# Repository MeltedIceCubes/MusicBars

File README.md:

# MusicBars
Tri-Channel Volume indicator board

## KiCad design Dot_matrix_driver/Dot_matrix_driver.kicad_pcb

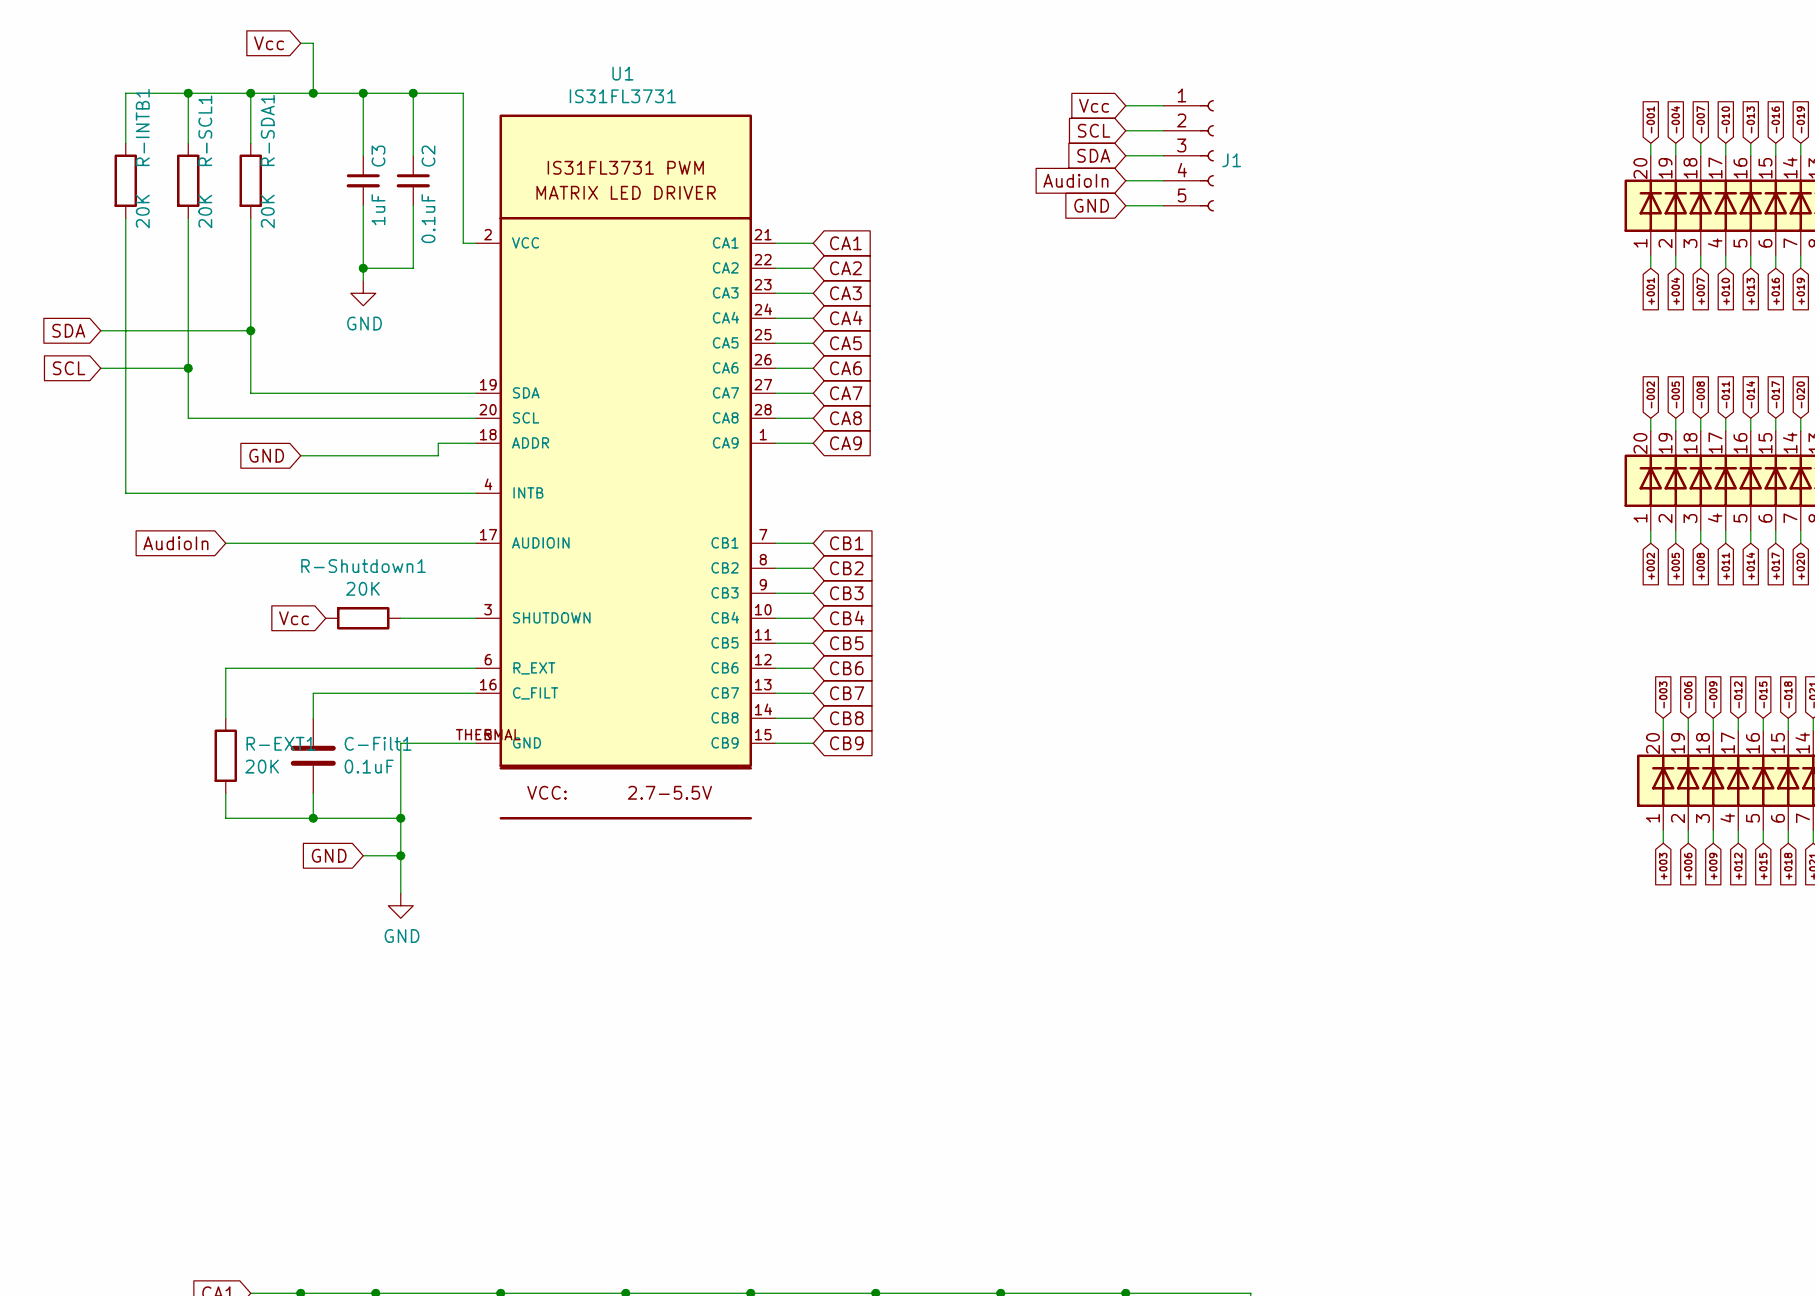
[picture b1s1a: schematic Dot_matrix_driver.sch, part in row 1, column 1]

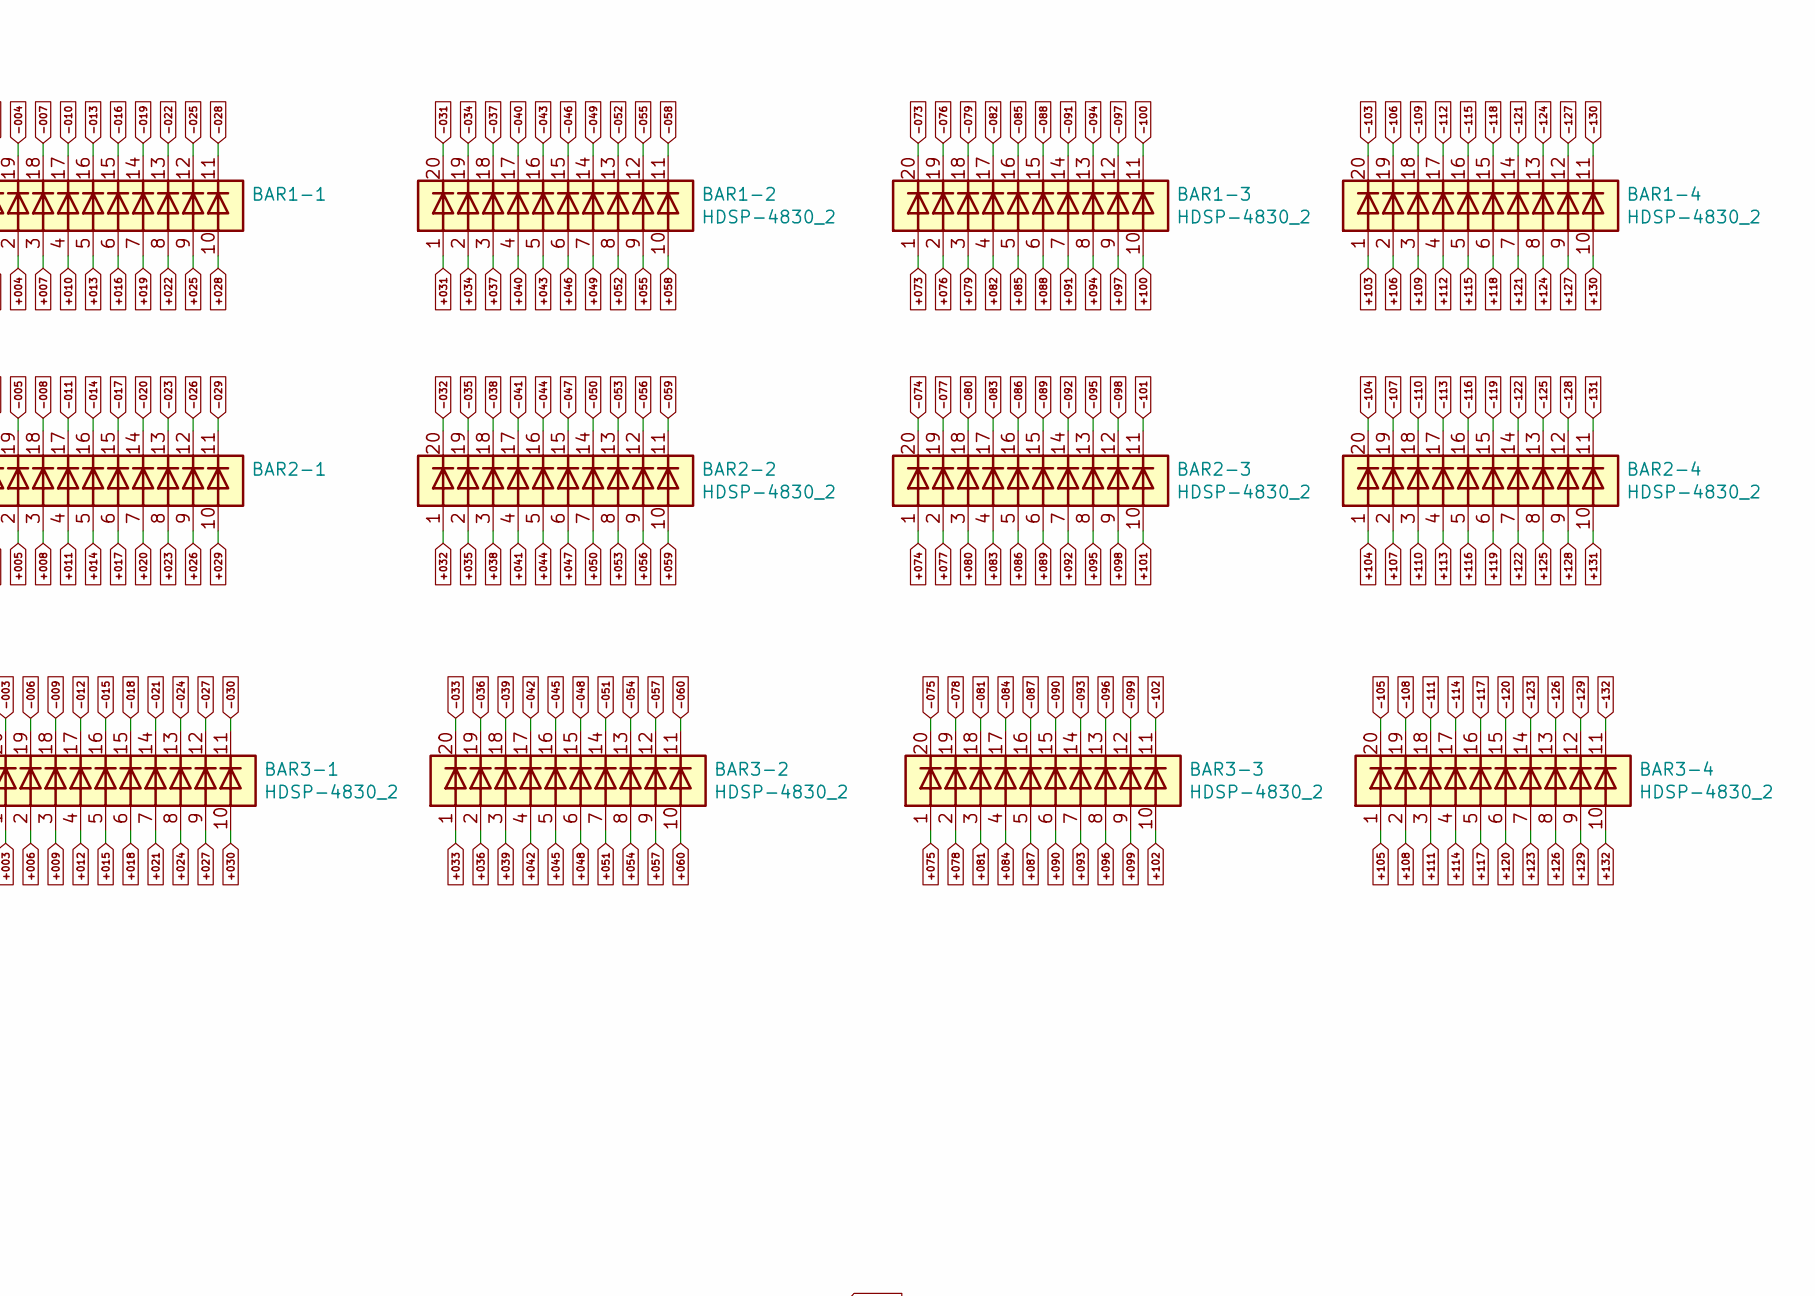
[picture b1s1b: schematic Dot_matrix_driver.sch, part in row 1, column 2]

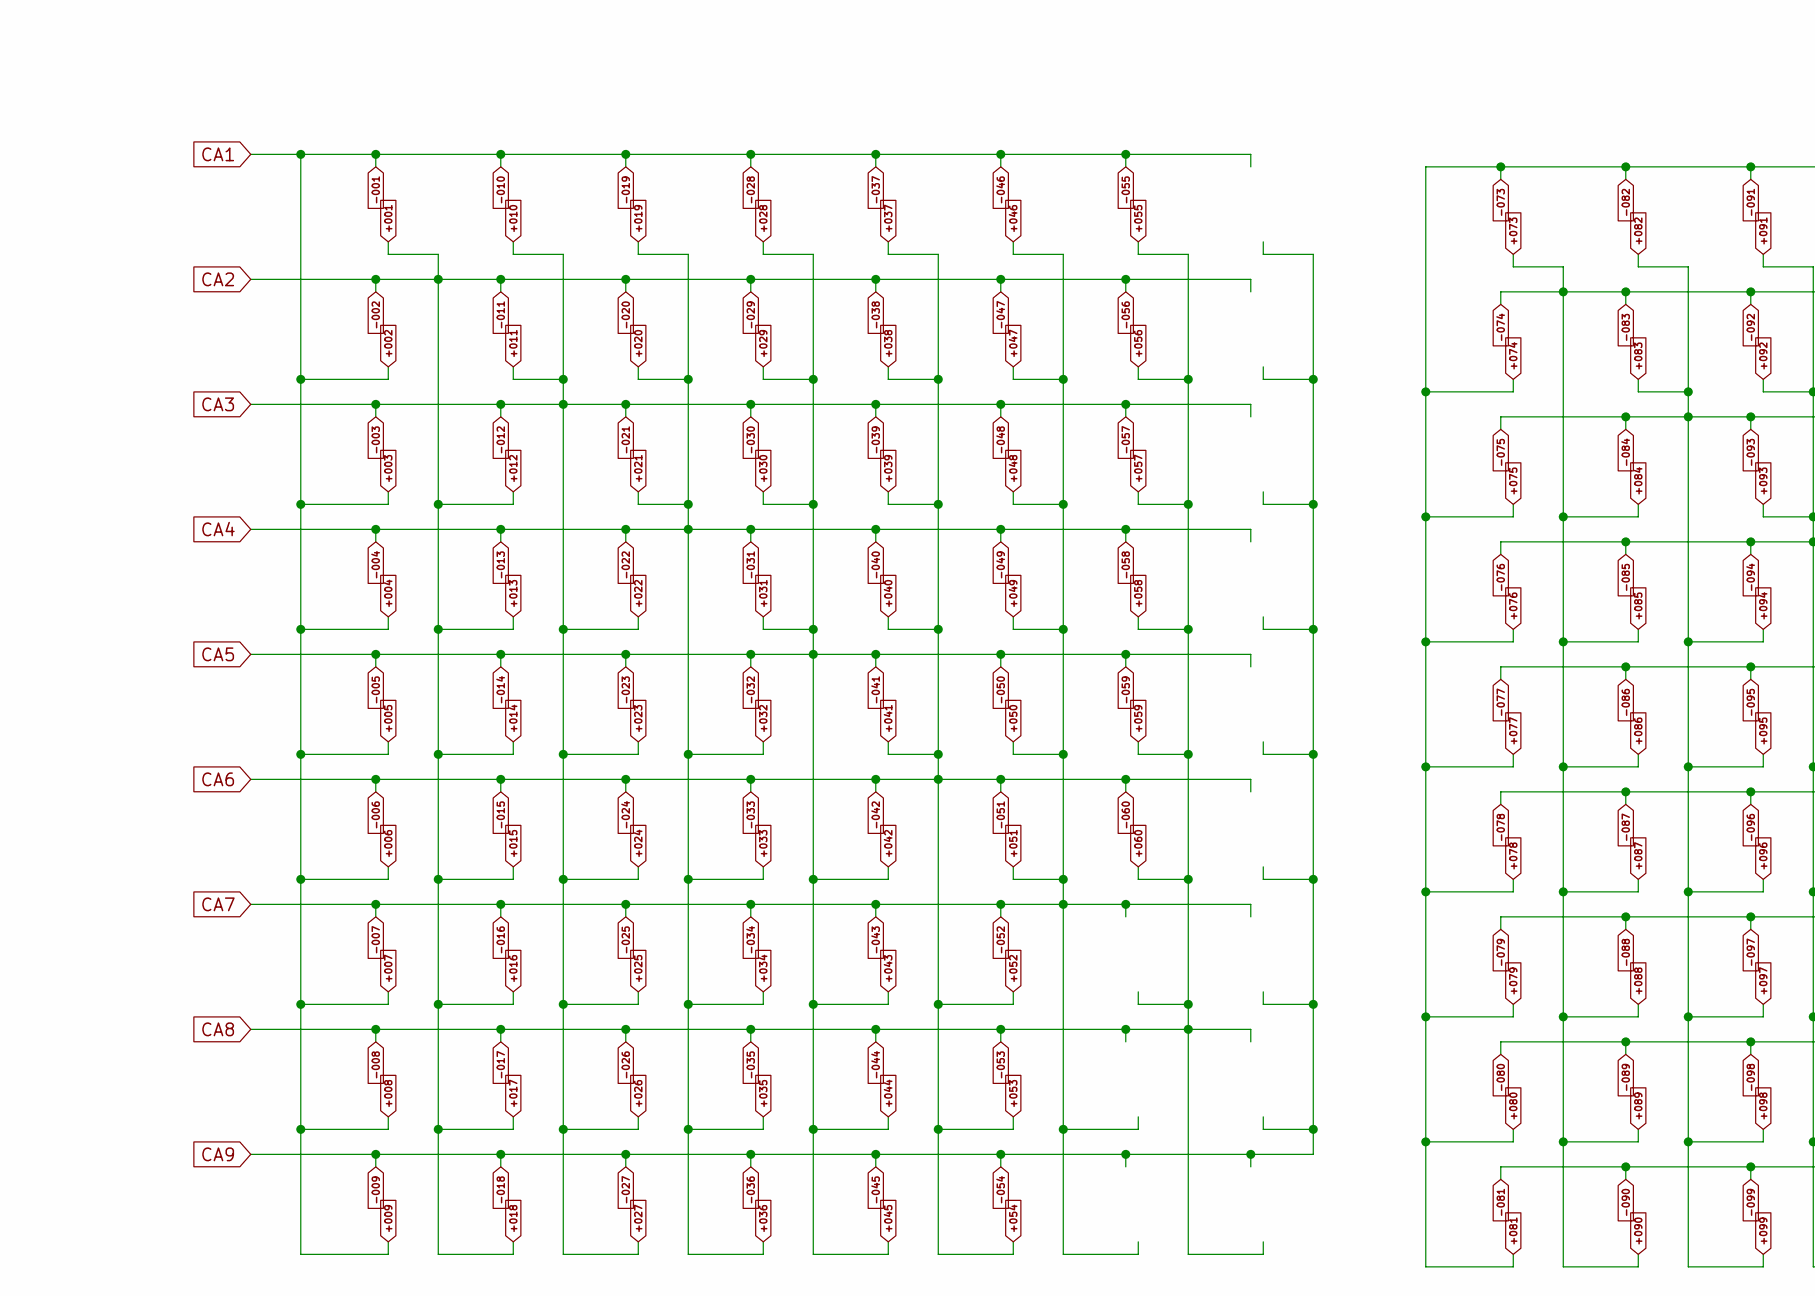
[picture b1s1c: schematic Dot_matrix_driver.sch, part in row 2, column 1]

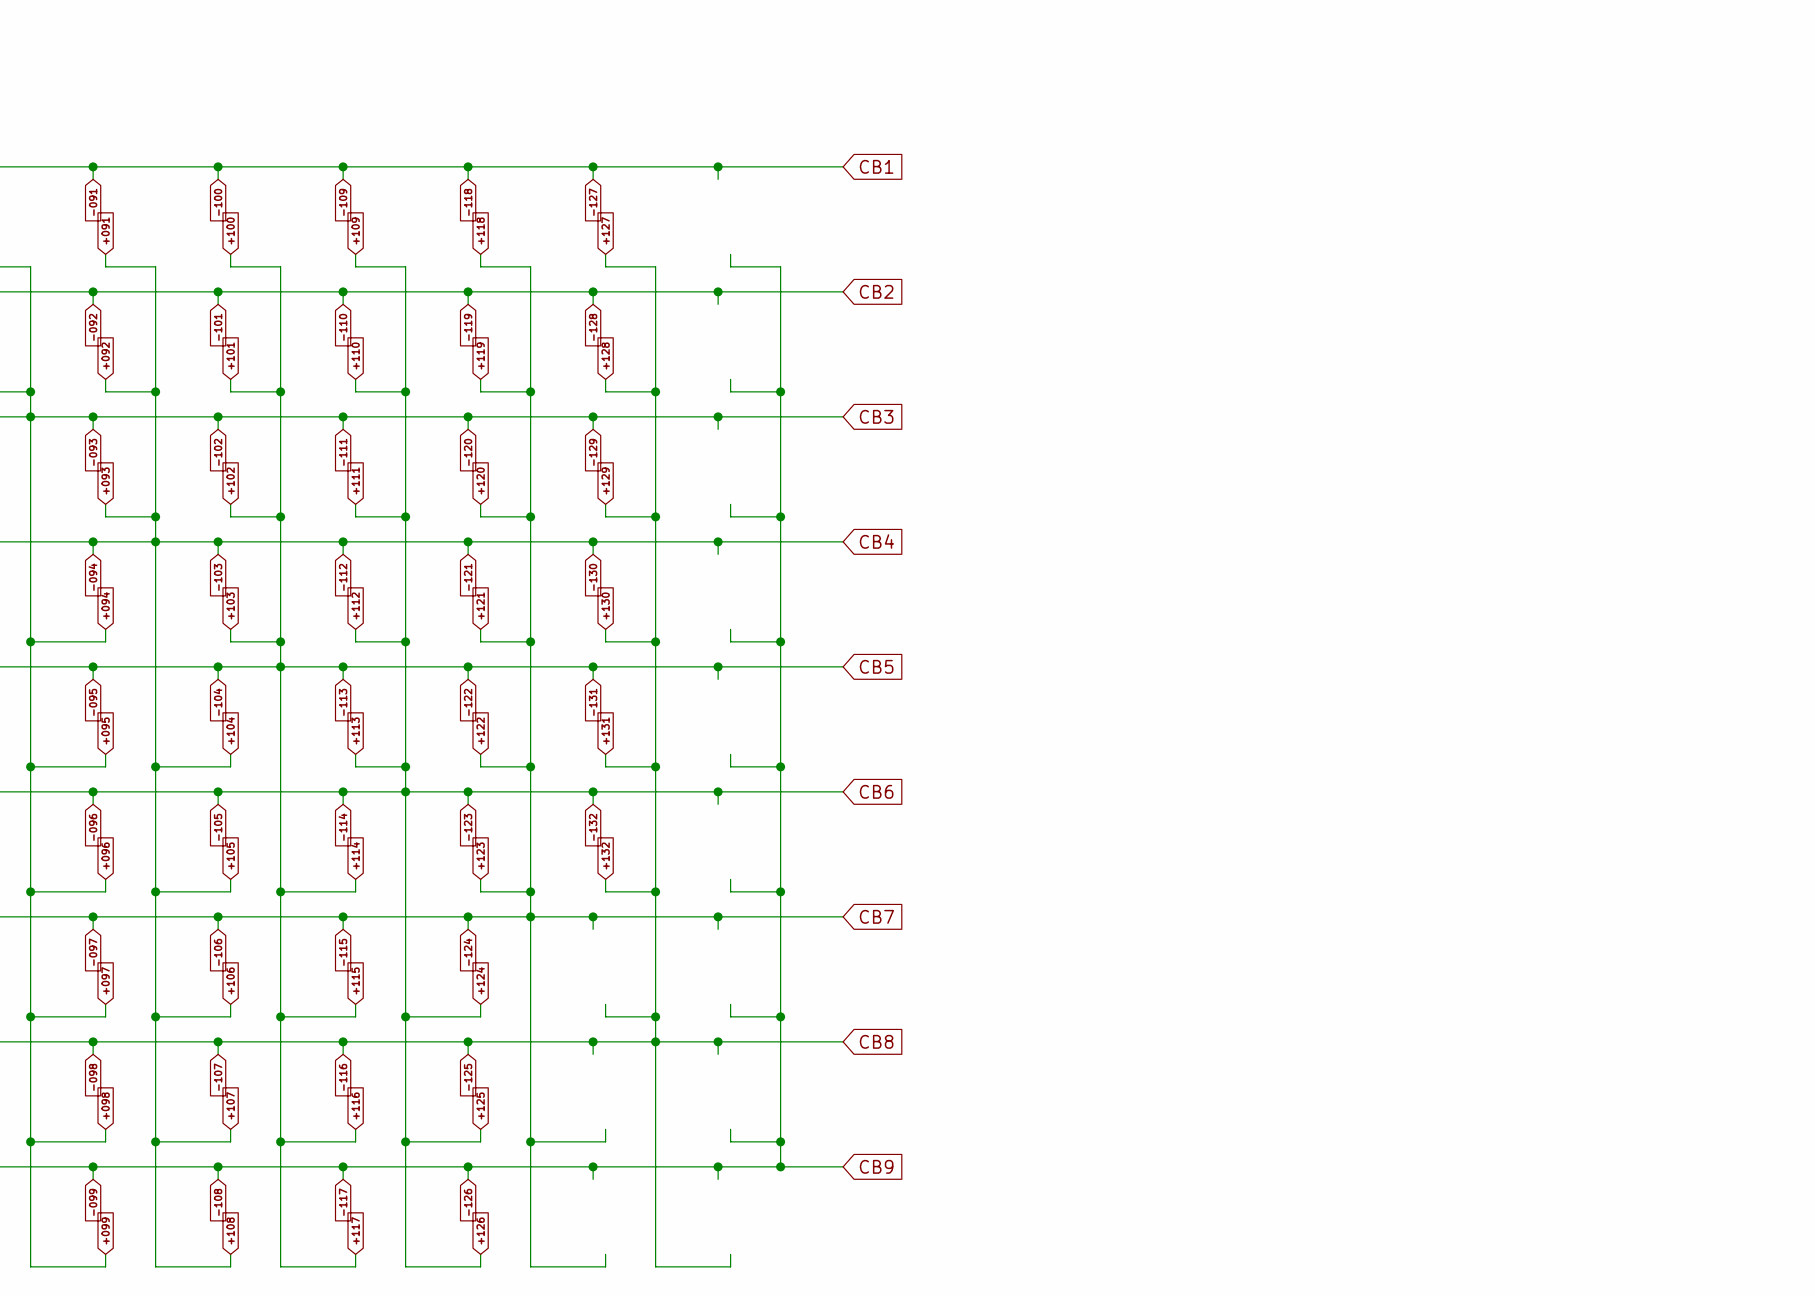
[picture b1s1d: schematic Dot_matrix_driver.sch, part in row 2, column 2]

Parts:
BAR1-1, BAR1-2, BAR1-3, BAR1-4, BAR2-1, BAR2-2, BAR2-3, BAR2-4, BAR3-1, BAR3-2, BAR3-3, BAR3-4: HDSP-4830_2; HDSP-48xx
C2: 0.1uF; C_Disc_D5.1mm_W3.2mm_P5.00mm
C3: 1uF; C_Disc_D5.1mm_W3.2mm_P5.00mm
C-Filt1: 0.1uF; C_Disc_D5.1mm_W3.2mm_P5.00mm
J1: Conn_01x05_Female; PinHeader_1x05_P2.54mm_Vertical
R-EXT1: 20K; R_Axial_DIN0207_L6.3mm_D2.5mm_P10.16mm_Horizontal
R-INTB1: 20K; R_Axial_DIN0207_L6.3mm_D2.5mm_P10.16mm_Horizontal
R-SCL1: 20K; R_Axial_DIN0207_L6.3mm_D2.5mm_P10.16mm_Horizontal
R-SDA1: 20K; R_Axial_DIN0207_L6.3mm_D2.5mm_P10.16mm_Horizontal
R-Shutdown1: 20K; R_Axial_DIN0207_L6.3mm_D2.5mm_P10.16mm_Horizontal
U1: IS31FL3731; QFN28_4MM_0.4MM

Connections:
+001: BAR1-1.1 (A), BAR1-1.5 (A), BAR1-1.6 (A), BAR2-1.5 (A), BAR2-1.6 (A), BAR2-1.11 (K), BAR2-1.14 (K), BAR2-1.17 (K), BAR2-1.20 (K), BAR2-2.12 (K), BAR2-2.15 (K), BAR2-2.18 (K), BAR3-1.4 (A), BAR3-1.5 (A), BAR3-1.6 (A), U1.22 (CA2)
+002: BAR1-1.2 (A), BAR1-1.3 (A), BAR1-1.11 (K), BAR1-1.14 (K), BAR1-1.17 (K), BAR1-1.20 (K), BAR1-2.12 (K), BAR1-2.15 (K), BAR1-2.18 (K), BAR2-1.1 (A), BAR2-1.2 (A), BAR2-1.3 (A), BAR3-1.1 (A), BAR3-1.2 (A), BAR3-1.3 (A), U1.21 (CA1)
+010: BAR1-1.4 (A), BAR1-1.8 (A), BAR1-1.9 (A), BAR2-1.4 (A), BAR2-1.8 (A), BAR2-1.9 (A), BAR3-1.8 (A), BAR3-1.9 (A), BAR3-1.11 (K), BAR3-1.14 (K), BAR3-1.17 (K), BAR3-1.20 (K), BAR3-2.12 (K), BAR3-2.15 (K), BAR3-2.18 (K), U1.23 (CA3)
+019: BAR1-1.7 (A), BAR1-1.13 (K), BAR1-1.16 (K), BAR1-1.19 (K), BAR1-2.2 (A), BAR1-2.11 (K), BAR1-2.14 (K), BAR1-2.17 (K), BAR1-2.20 (K), BAR2-1.7 (A), BAR2-2.1 (A), BAR2-2.2 (A), BAR3-1.7 (A), BAR3-2.1 (A), BAR3-2.2 (A), U1.24 (CA4)
+028: BAR1-1.10 (A), BAR1-2.1 (A), BAR1-2.5 (A), BAR2-1.10 (A), BAR2-1.13 (K), BAR2-1.16 (K), BAR2-1.19 (K), BAR2-2.5 (A), BAR2-2.11 (K), BAR2-2.14 (K), BAR2-2.17 (K), BAR2-2.20 (K), BAR3-1.10 (A), BAR3-2.4 (A), BAR3-2.5 (A), U1.25 (CA5)
+037: BAR1-2.3 (A), BAR1-2.4 (A), BAR1-2.8 (A), BAR2-2.3 (A), BAR2-2.4 (A), BAR2-2.8 (A), BAR3-1.13 (K), BAR3-1.16 (K), BAR3-1.19 (K), BAR3-2.3 (A), BAR3-2.8 (A), BAR3-2.11 (K), BAR3-2.14 (K), BAR3-2.17 (K), BAR3-2.20 (K), U1.26 (CA6)
+046: BAR1-1.12 (K), BAR1-1.15 (K), BAR1-1.18 (K), BAR1-2.6 (A), BAR1-2.7 (A), BAR1-2.13 (K), BAR1-2.16 (K), BAR1-2.19 (K), BAR2-2.6 (A), BAR2-2.7 (A), BAR3-2.6 (A), BAR3-2.7 (A), U1.27 (CA7)
+055: BAR1-2.9 (A), BAR1-2.10 (A), BAR2-1.12 (K), BAR2-1.15 (K), BAR2-1.18 (K), BAR2-2.9 (A), BAR2-2.10 (A), BAR2-2.13 (K), BAR2-2.16 (K), BAR2-2.19 (K), BAR3-2.9 (A), BAR3-2.10 (A), U1.28 (CA8)
+073: BAR1-3.1 (A), BAR1-3.5 (A), BAR1-3.6 (A), BAR2-3.5 (A), BAR2-3.6 (A), BAR2-3.11 (K), BAR2-3.14 (K), BAR2-3.17 (K), BAR2-3.20 (K), BAR2-4.12 (K), BAR2-4.15 (K), BAR2-4.18 (K), BAR3-3.4 (A), BAR3-3.5 (A), BAR3-3.6 (A), U1.8 (CB2)
+074: BAR1-3.2 (A), BAR1-3.3 (A), BAR1-3.11 (K), BAR1-3.14 (K), BAR1-3.17 (K), BAR1-3.20 (K), BAR1-4.12 (K), BAR1-4.15 (K), BAR1-4.18 (K), BAR2-3.1 (A), BAR2-3.2 (A), BAR2-3.3 (A), BAR3-3.1 (A), BAR3-3.2 (A), BAR3-3.3 (A), U1.7 (CB1)
+082: BAR1-3.4 (A), BAR1-3.8 (A), BAR1-3.9 (A), BAR2-3.4 (A), BAR2-3.8 (A), BAR2-3.9 (A), BAR3-3.8 (A), BAR3-3.9 (A), BAR3-3.11 (K), BAR3-3.14 (K), BAR3-3.17 (K), BAR3-3.20 (K), BAR3-4.12 (K), BAR3-4.15 (K), BAR3-4.18 (K), U1.9 (CB3)
+091: BAR1-3.7 (A), BAR1-3.13 (K), BAR1-3.16 (K), BAR1-3.19 (K), BAR1-4.2 (A), BAR1-4.11 (K), BAR1-4.14 (K), BAR1-4.17 (K), BAR1-4.20 (K), BAR2-3.7 (A), BAR2-4.1 (A), BAR2-4.2 (A), BAR3-3.7 (A), BAR3-4.1 (A), BAR3-4.2 (A), U1.10 (CB4)
+100: BAR1-3.10 (A), BAR1-4.1 (A), BAR1-4.5 (A), BAR2-3.10 (A), BAR2-3.13 (K), BAR2-3.16 (K), BAR2-3.19 (K), BAR2-4.5 (A), BAR2-4.11 (K), BAR2-4.14 (K), BAR2-4.17 (K), BAR2-4.20 (K), BAR3-3.10 (A), BAR3-4.4 (A), BAR3-4.5 (A), U1.11 (CB5)
+109: BAR1-4.3 (A), BAR1-4.4 (A), BAR1-4.8 (A), BAR2-4.3 (A), BAR2-4.4 (A), BAR2-4.8 (A), BAR3-3.13 (K), BAR3-3.16 (K), BAR3-3.19 (K), BAR3-4.3 (A), BAR3-4.8 (A), BAR3-4.11 (K), BAR3-4.14 (K), BAR3-4.17 (K), BAR3-4.20 (K), U1.12 (CB6)
+118: BAR1-3.12 (K), BAR1-3.15 (K), BAR1-3.18 (K), BAR1-4.6 (A), BAR1-4.7 (A), BAR1-4.13 (K), BAR1-4.16 (K), BAR1-4.19 (K), BAR2-4.6 (A), BAR2-4.7 (A), BAR3-4.6 (A), BAR3-4.7 (A), U1.13 (CB7)
+127: BAR1-4.9 (A), BAR1-4.10 (A), BAR2-3.12 (K), BAR2-3.15 (K), BAR2-3.18 (K), BAR2-4.9 (A), BAR2-4.10 (A), BAR2-4.13 (K), BAR2-4.16 (K), BAR2-4.19 (K), BAR3-4.9 (A), BAR3-4.10 (A), U1.14 (CB8)
-009: BAR3-1.12 (K), BAR3-1.15 (K), BAR3-1.18 (K), BAR3-2.13 (K), BAR3-2.16 (K), BAR3-2.19 (K), U1.1 (CA9)
-081: BAR3-3.12 (K), BAR3-3.15 (K), BAR3-3.18 (K), BAR3-4.13 (K), BAR3-4.16 (K), BAR3-4.19 (K), U1.15 (CB9)
AudioIn: J1.4, U1.17 (AUDIOIN)
GND: C2.2, C3.2, C-Filt1.2, J1.5, R-EXT1.2, U1.5 (GND), U1.18 (ADDR), U1.THERMAL (GND)
unnamed: C-Filt1.1, U1.16 (C_FILT)
unnamed: R-EXT1.1, U1.6 (R_EXT)
unnamed: R-INTB1.2, U1.4 (INTB)
unnamed: R-Shutdown1.1, U1.3 (SHUTDOWN)
SCL: J1.2, R-SCL1.2, U1.20 (SCL)
SDA: J1.3, R-SDA1.2, U1.19 (SDA)
Vcc: C2.1, C3.1, J1.1, R-INTB1.1, R-SCL1.1, R-SDA1.1, R-Shutdown1.2, U1.2 (VCC)

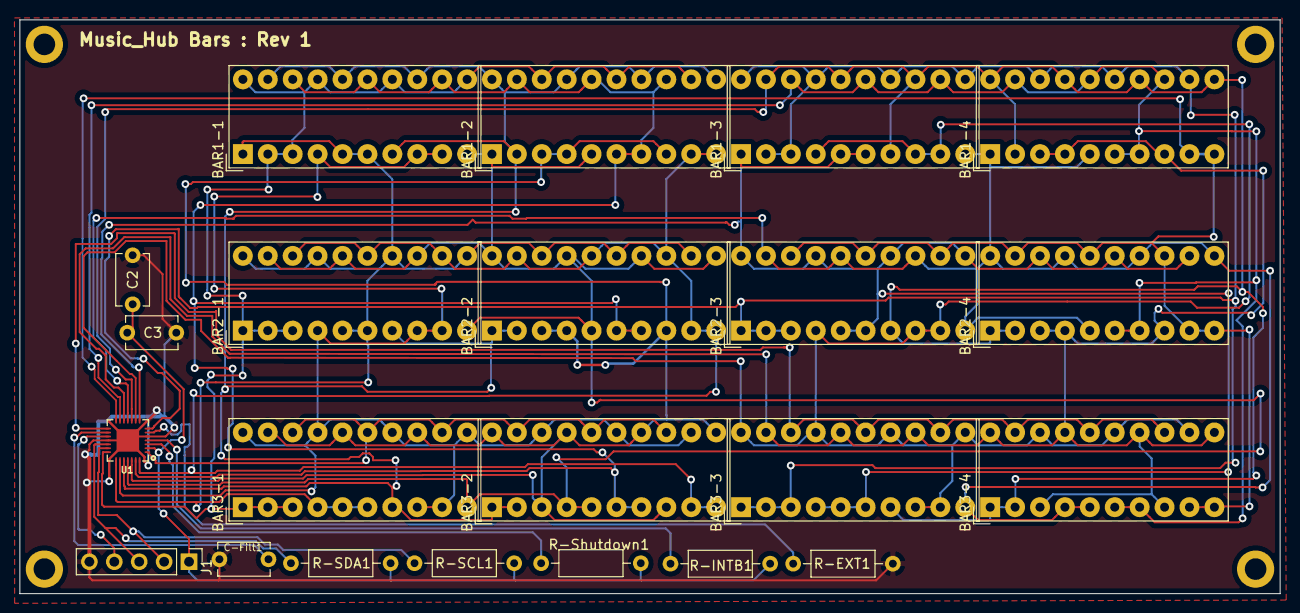
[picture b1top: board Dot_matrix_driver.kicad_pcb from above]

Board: 2 copper layers, 128.5 x 58.5 mm, 22 parts (0 on the bottom side), 27 nets.

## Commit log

2023-03-06 KiCAD Files for music bar PCB
    Just my one commit for all the KiCAD files
